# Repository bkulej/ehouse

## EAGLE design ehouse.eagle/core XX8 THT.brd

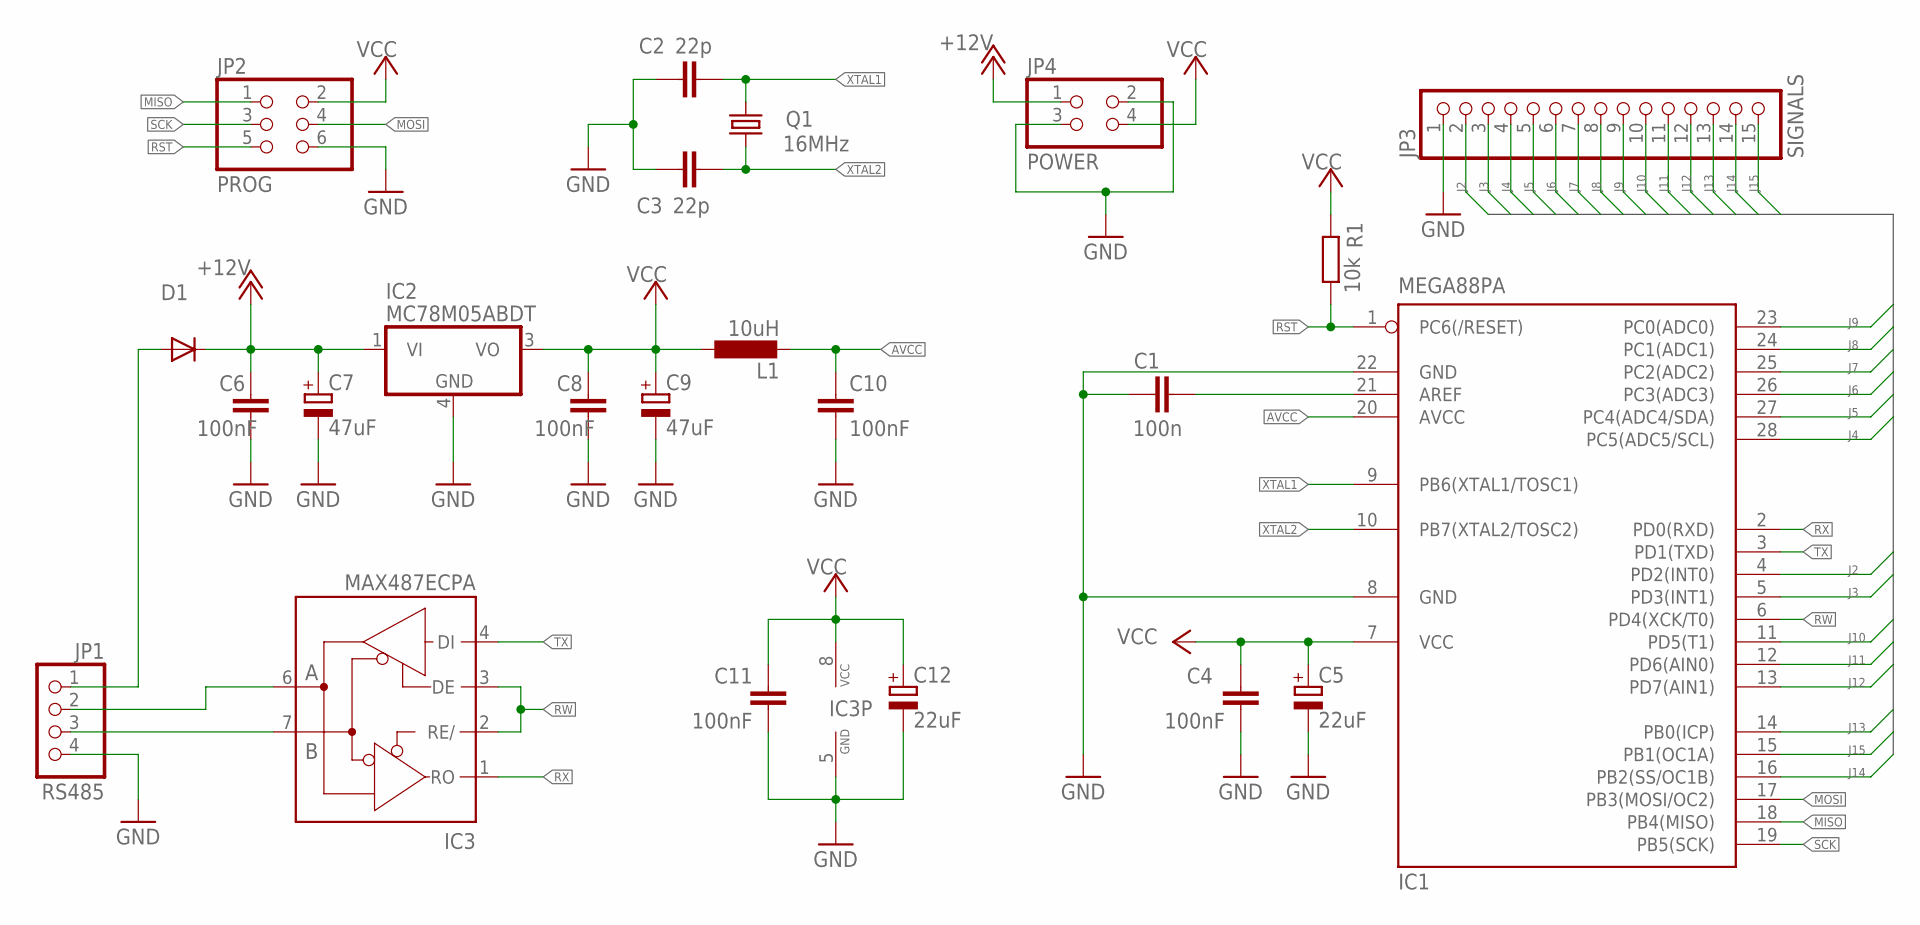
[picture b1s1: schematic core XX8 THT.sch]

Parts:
C1: 100n; C025-024X044
C2, C3: 22p; C025-024X044
C4, C6, C8, C10, C11: 100nF; C025-025X050
C5, C12: 22uF; E2-5
C7, C9: 47uF; E2,5-6
D1: 1N4002; DO34-7
IC1: MEGA88PA; DIL28-3
IC2: MC78M05ABDT; DPACK_3
IC3: MAX487ECPA; DIL08
JP1: RS485; 1X04
JP2: PROG; 2X03
JP3: SIGNALS; 1X15
JP4: POWER; 2X02
L1: 10uH; 0207/12
Q1: 16MHz; HC49/S
R1: 10k; 0204V

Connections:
+12V: C6.1, C7.+, D1.C, IC2.1 (VI), JP4.1
AVCC: C10.1, IC1.20 (AVCC), L1.2
GND: C1.1, C2.1, C3.1, C4.2, C5.-, C6.2, C7.-, C8.2, C9.-, C10.2, C11.2, C12.-, IC1.8 (GND), IC1.22 (GND), IC2.4 (GND), IC3.5 (GND), JP1.4, JP2.6, JP3.1, JP4.2, JP4.3
J2: IC1.4 (PD2(INT0)), JP3.2
J3: IC1.5 (PD3(INT1)), JP3.3
J4: IC1.28 (PC5(ADC5/SCL)), JP3.4
J5: IC1.27 (PC4(ADC4/SDA)), JP3.5
J6: IC1.26 (PC3(ADC3)), JP3.6
J7: IC1.25 (PC2(ADC2)), JP3.7
J8: IC1.24 (PC1(ADC1)), JP3.8
J9: IC1.23 (PC0(ADC0)), JP3.9
J10: IC1.11 (PD5(T1)), JP3.10
J11: IC1.12 (PD6(AIN0)), JP3.11
J12: IC1.13 (PD7(AIN1)), JP3.12
J13: IC1.14 (PB0(ICP)), JP3.13
J14: IC1.16 (PB2(SS/OC1B)), JP3.14
J15: IC1.15 (PB1(OC1A)), JP3.15
MISO: IC1.18 (PB4(MISO)), JP2.1
MOSI: IC1.17 (PB3(MOSI/OC2)), JP2.4
unnamed: C1.2, IC1.21 (AREF)
unnamed: D1.A, JP1.1
unnamed: IC3.7 (B), JP1.3
unnamed: IC3.6 (A), JP1.2
RST: IC1.1 (PC6(/RESET)), JP2.5, R1.1
RW: IC1.6 (PD4(XCK/T0)), IC3.2 (RE/), IC3.3 (DE)
RX: IC1.2 (PD0(RXD)), IC3.1 (RO)
SCK: IC1.19 (PB5(SCK)), JP2.3
TX: IC1.3 (PD1(TXD)), IC3.4 (DI)
VCC: C4.1, C5.+, C8.1, C9.+, C11.1, C12.+, IC1.7 (VCC), IC2.3 (VO), IC3.8 (VCC), JP2.2, JP4.4, L1.1, R1.2
XTAL1: C2.2, IC1.9 (PB6(XTAL1/TOSC1)), Q1.2
XTAL2: C3.2, IC1.10 (PB7(XTAL2/TOSC2)), Q1.1

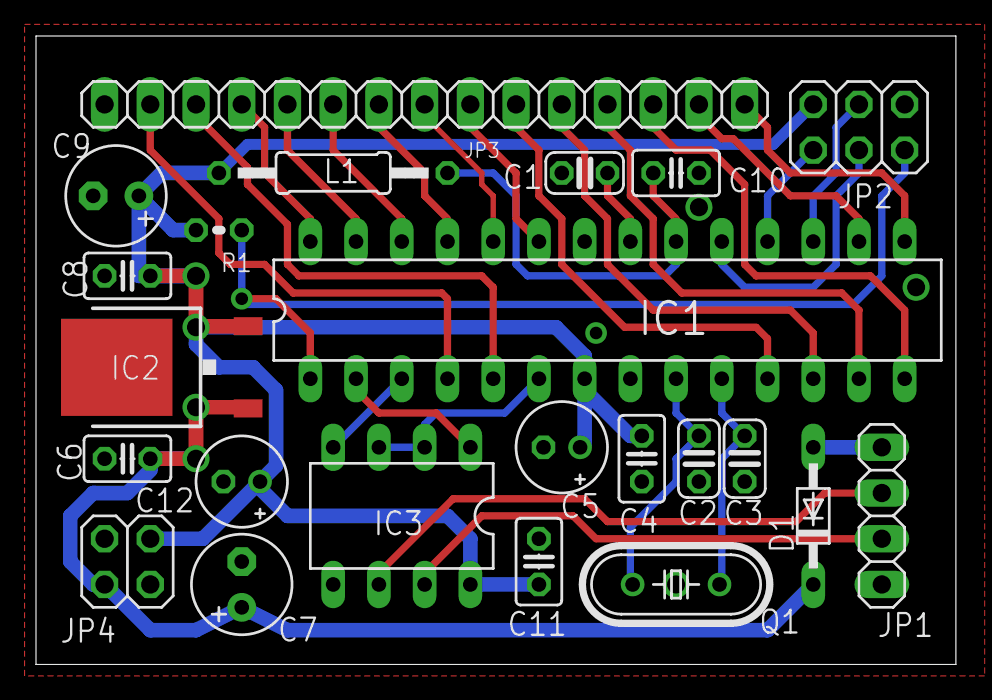
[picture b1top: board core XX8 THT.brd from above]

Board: 2 copper layers, 51.1 x 34.9 mm, 23 parts (0 on the bottom side), 31 nets.

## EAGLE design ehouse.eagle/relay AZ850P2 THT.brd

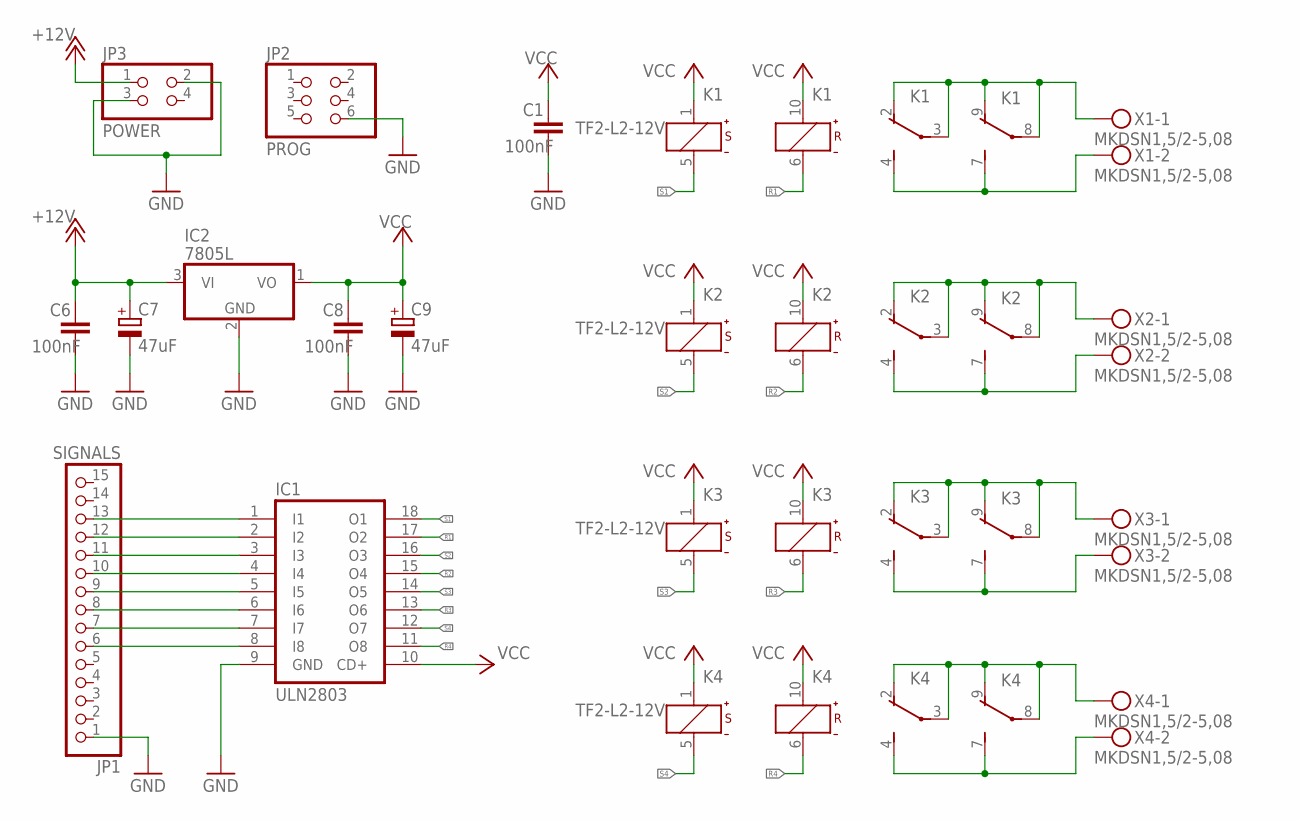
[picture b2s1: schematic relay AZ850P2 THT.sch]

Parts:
C1, C6, C8: 100nF; C025-025X050
C7, C9: 47uF; E2,5-6
IC1: ULN2803; DIL18
IC2: 7805L; TO92
JP1: SIGNALS; 1X15
JP2: PROG; 2X03
JP3: POWER; 2X02
K1, K2, K3, K4: TF2-L2-12V; TF2
X1, X2, X3, X4: MKDSN1,5/2-5,08

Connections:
+12V: C6.1, C7.+, IC2.3 (VI), JP3.1
GND: C1.2, C6.2, C7.-, C8.2, C9.-, IC1.9 (GND), IC2.2 (GND), JP1.1, JP2.6, JP3.2, JP3.3
unnamed: IC1.1 (I1), JP1.13
unnamed: IC1.2 (I2), JP1.12
unnamed: IC1.3 (I3), JP1.11
unnamed: IC1.4 (I4), JP1.10
unnamed: IC1.5 (I5), JP1.9
unnamed: IC1.6 (I6), JP1.8
unnamed: IC1.7 (I7), JP1.7
unnamed: IC1.8 (I8), JP1.6
unnamed: K1.2 (O), K1.3, K1.8, K1.9 (O), X1.1
unnamed: K1.4 (S), K1.7 (S), X1.2
unnamed: K2.2 (O), K2.3, K2.8, K2.9 (O), X2.1
unnamed: K2.4 (S), K2.7 (S), X2.2
unnamed: K3.2 (O), K3.3, K3.8, K3.9 (O), X3.1
unnamed: K3.4 (S), K3.7 (S), X3.2
unnamed: K4.4 (S), K4.7 (S), X4.2
unnamed: K4.2 (O), K4.3, K4.8, K4.9 (O), X4.1
R1: IC1.17 (O2), K1.6 (-)
R2: IC1.15 (O4), K2.6 (-)
R3: IC1.13 (O6), K3.6 (-)
R4: IC1.11 (O8), K4.6 (-)
S1: IC1.18 (O1), K1.5 (-)
S2: IC1.16 (O3), K2.5 (-)
S3: IC1.14 (O5), K3.5 (-)
S4: IC1.12 (O7), K4.5 (-)
VCC: C1.1, C8.1, C9.+, IC1.10 (CD+), IC2.1 (VO), K1.1 (+), K1.10 (+), K2.1 (+), K2.10 (+), K3.1 (+), K3.10 (+), K4.1 (+), K4.10 (+)

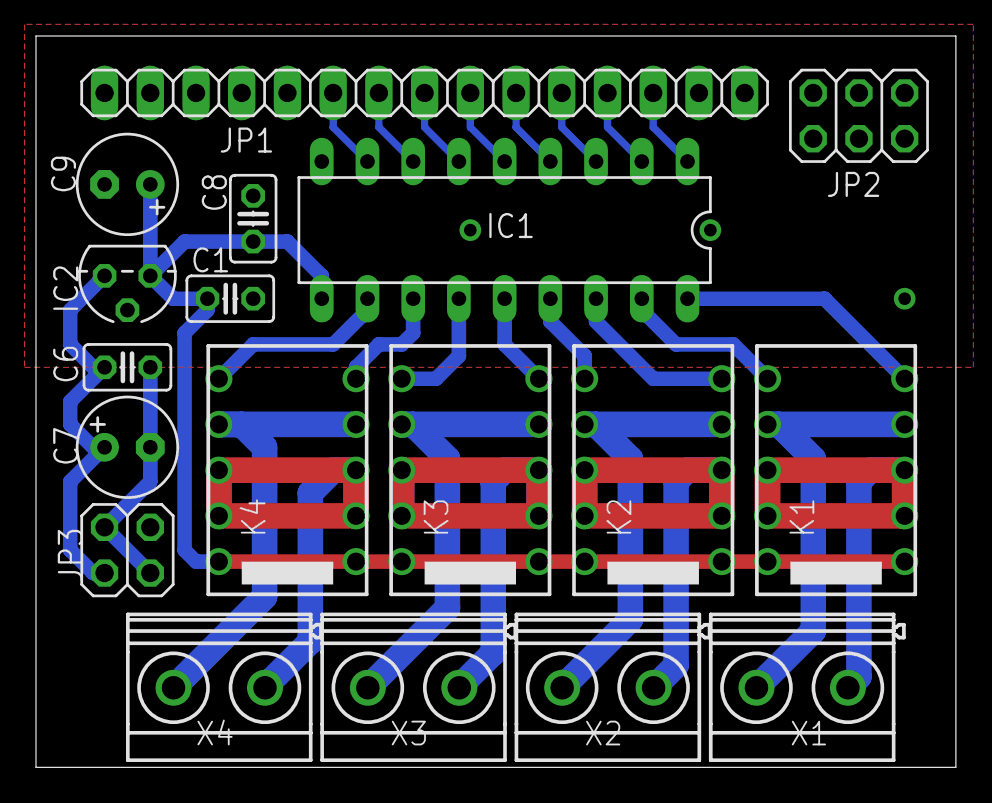
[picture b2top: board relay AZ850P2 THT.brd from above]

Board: 2 copper layers, 51.1 x 40.6 mm, 18 parts (0 on the bottom side), 27 nets.

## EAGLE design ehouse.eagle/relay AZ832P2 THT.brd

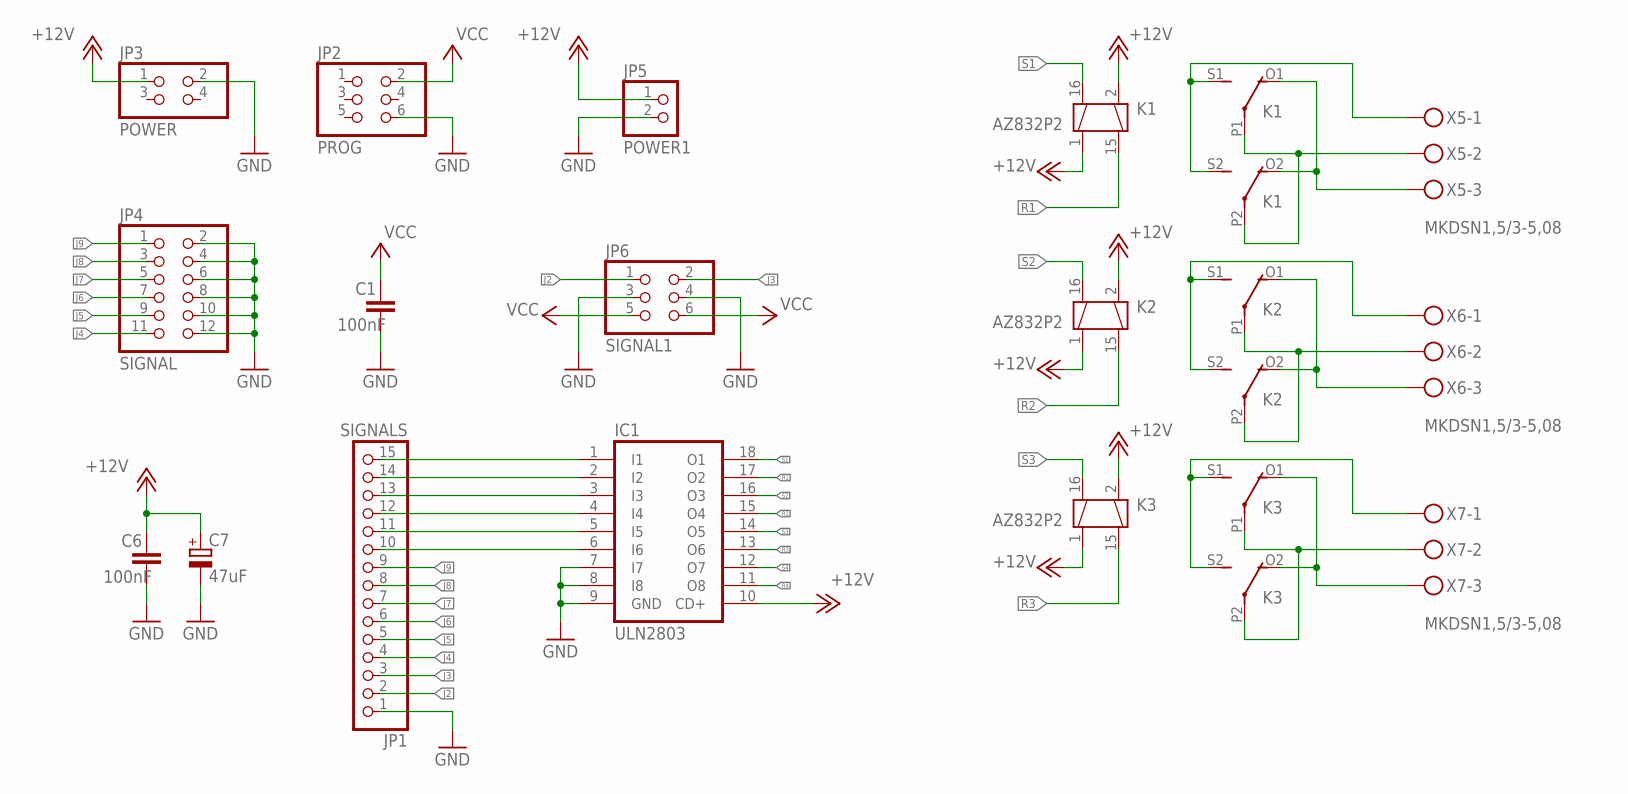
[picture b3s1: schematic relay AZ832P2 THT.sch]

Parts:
C1, C6: 100nF; C025-025X050
C7: 47uF; E2,5-6
IC1: ULN2803; DIL18
JP1: SIGNALS; 1X15
JP2: PROG; 2X03
JP3: POWER; 2X02
JP4: SIGNAL; 2X06
JP5: POWER1; 1X02
JP6: SIGNAL1; 2X03
K1, K2, K3: AZ832P2; DS2E-L2
X5, X6, X7: MKDSN1,5/3-5,08

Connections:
+12V: C6.1, C7.+, IC1.10 (CD+), JP3.1, JP5.1, K1.1 (2), K1.2 (3), K2.1 (2), K2.2 (3), K3.1 (2), K3.2 (3)
GND: C1.2, C6.2, C7.-, IC1.7 (I7), IC1.8 (I8), IC1.9 (GND), JP1.1, JP2.6, JP3.2, JP4.2, JP4.4, JP4.6, JP4.8, JP4.10, JP4.12, JP5.2, JP6.3, JP6.4
J2: JP1.2, JP6.1
J3: JP1.3, JP6.2
J4: JP1.4, JP4.11
J5: JP1.5, JP4.9
J6: JP1.6, JP4.7
J7: JP1.7, JP4.5
J8: JP1.8, JP4.3
J9: JP1.9, JP4.1
unnamed: IC1.1 (I1), JP1.15
unnamed: IC1.2 (I2), JP1.14
unnamed: IC1.3 (I3), JP1.13
unnamed: IC1.4 (I4), JP1.12
unnamed: IC1.5 (I5), JP1.11
unnamed: IC1.6 (I6), JP1.10
unnamed: K1.S1 (S), K1.S2 (S), X5.1
unnamed: K2.S1 (S), K2.S2 (S), X6.1
unnamed: K3.S1 (S), K3.S2 (S), X7.1
unnamed: K3.P1, K3.P2, X7.2
unnamed: K2.P1, K2.P2, X6.2
unnamed: K1.O1 (O), K1.O2 (O), X5.3
unnamed: K2.O1 (O), K2.O2 (O), X6.3
unnamed: K1.P1, K1.P2, X5.2
unnamed: K3.O1 (O), K3.O2 (O), X7.3
R1: IC1.17 (O2), K1.15 (4)
R2: IC1.15 (O4), K2.15 (4)
R3: IC1.13 (O6), K3.15 (4)
R4: IC1.11 (O8)
S1: IC1.18 (O1), K1.16 (1)
S2: IC1.16 (O3), K2.16 (1)
S3: IC1.14 (O5), K3.16 (1)
S4: IC1.12 (O7)
VCC: C1.1, JP2.2, JP6.5, JP6.6

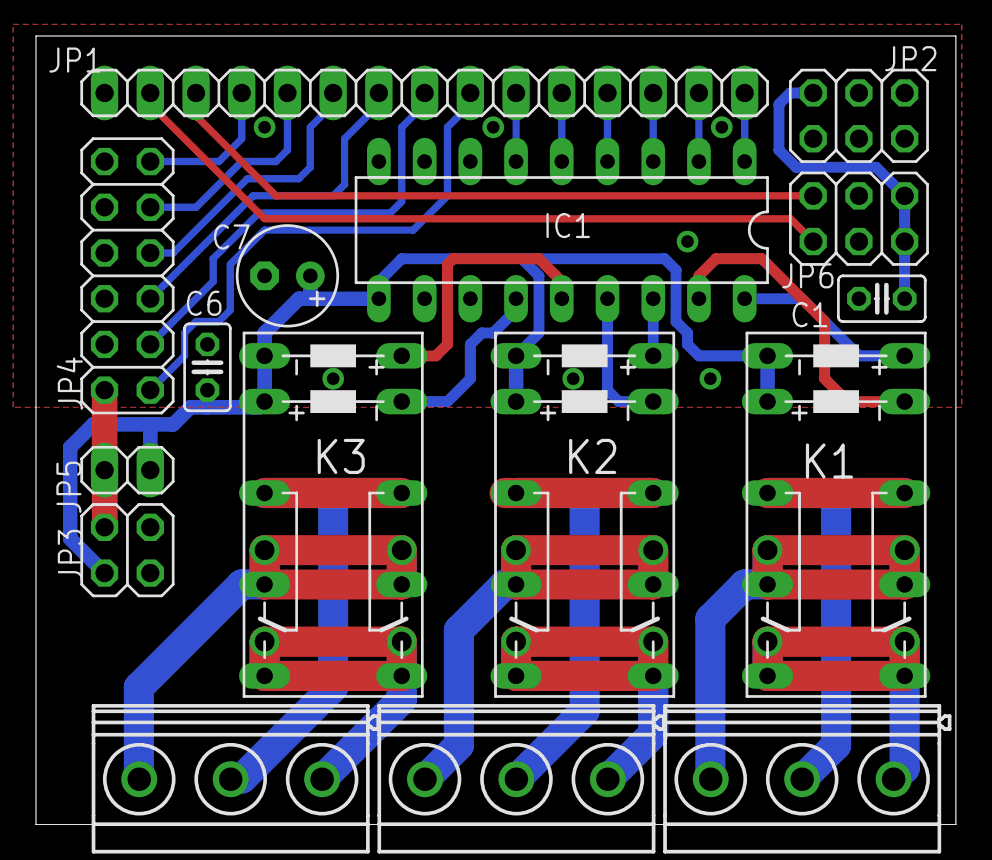
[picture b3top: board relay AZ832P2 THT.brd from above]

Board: 2 copper layers, 51.1 x 43.8 mm, 16 parts (0 on the bottom side), 32 nets.

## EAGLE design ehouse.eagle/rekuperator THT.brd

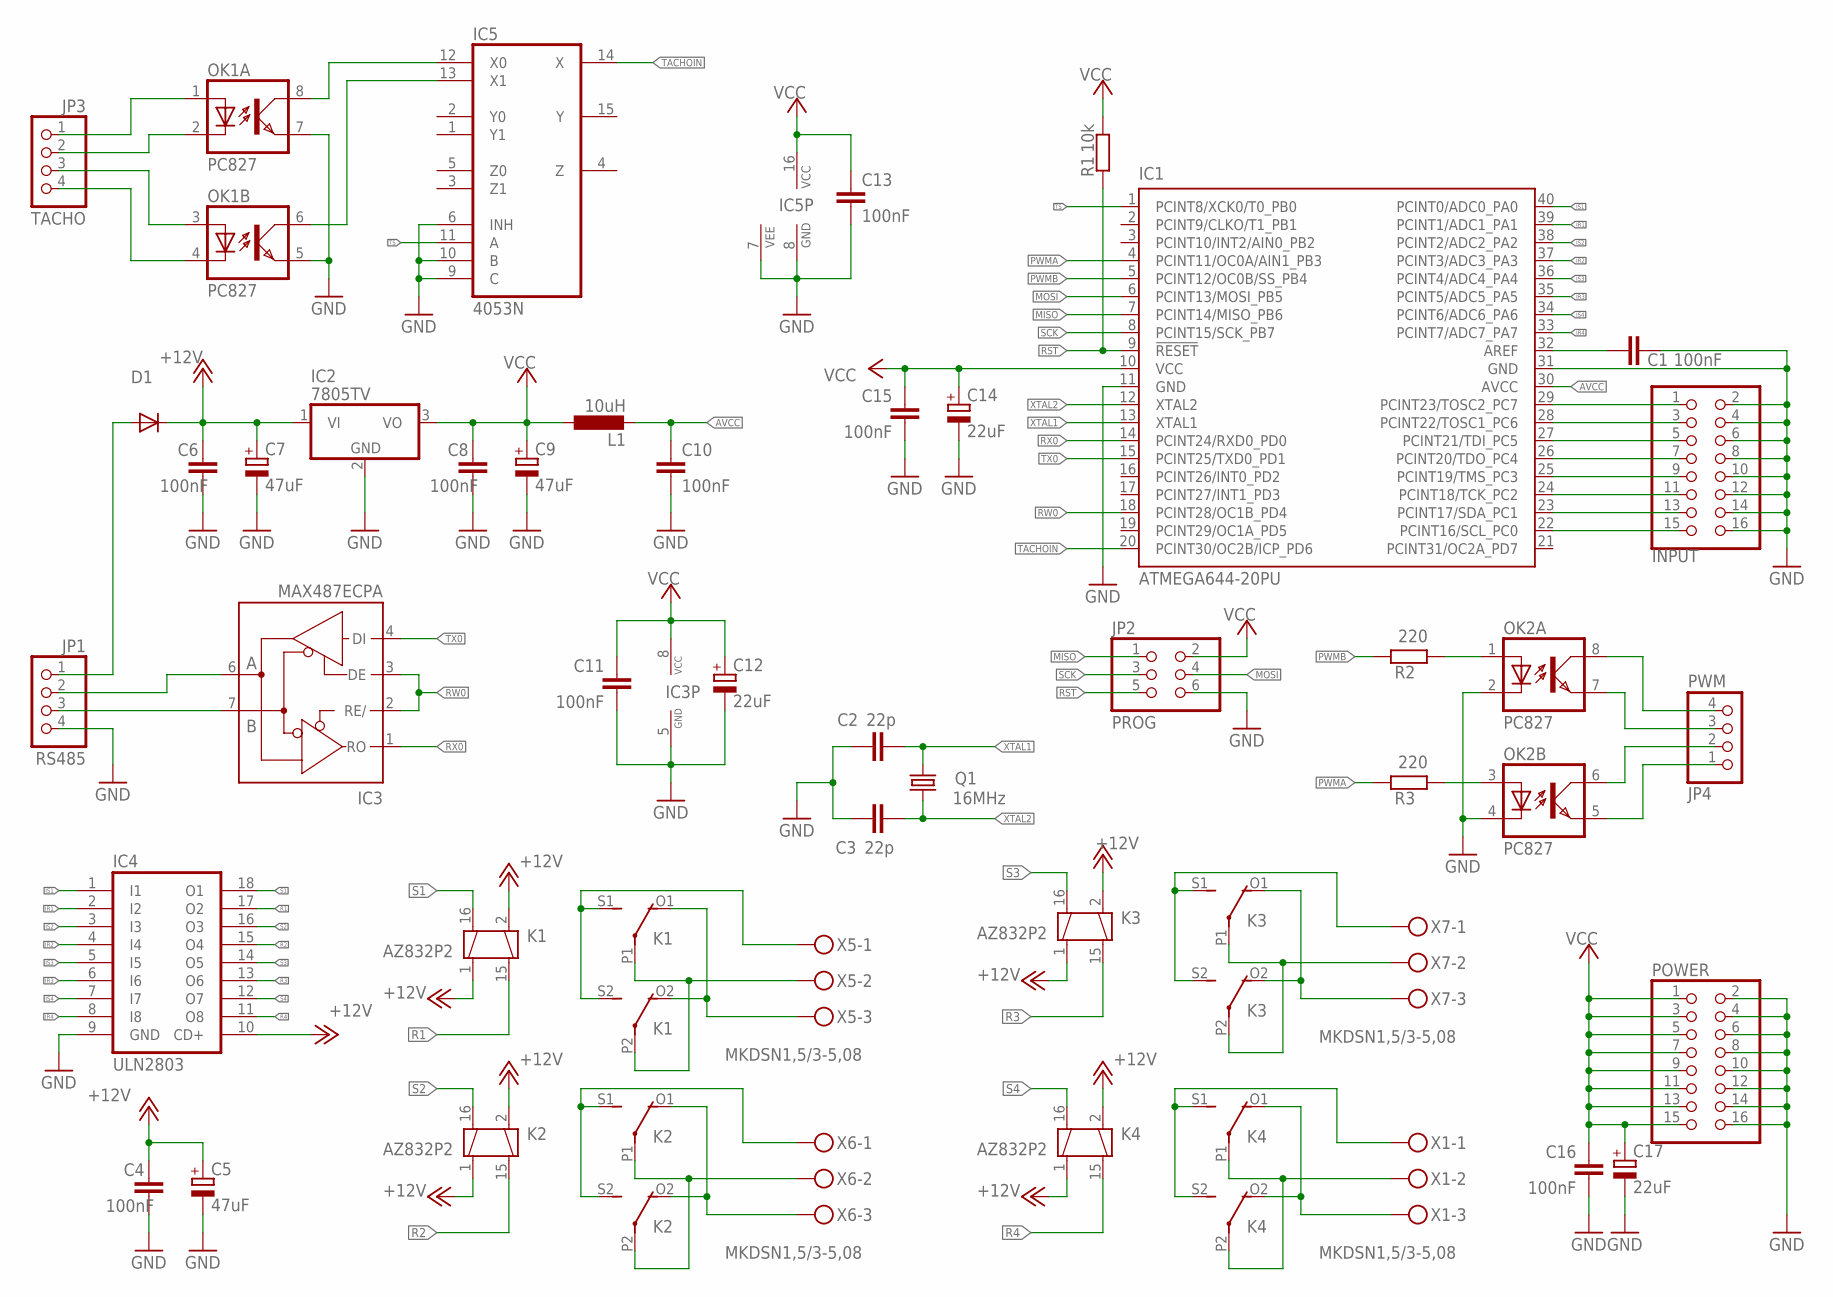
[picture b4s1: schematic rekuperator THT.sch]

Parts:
C1, C4, C6, C8, C10, C11, C13, C15, C16: 100nF; C025-025X050
C2, C3: 22p; C025-024X044
C5, C7, C9: 47uF; E2,5-6
C12, C14, C17: 22uF; E2-5
D1: 1N4002; DO34-7
IC1: ATMEGA644-20PU; DIL40
IC2: 7805TV; TO220V
IC3: MAX487ECPA; DIL08
IC4: ULN2803; DIL18
IC5: 4053N; DIL16
INPUT: PINHD-2X8; 2X08
JP1: RS485; 1X04
JP2: PROG; 2X03
JP3: TACHO; 1X04
JP4: PWM; 1X04
K1, K2, K3, K4: AZ832P2; DS2E-L2
L1: 10uH; 0207/12
OK1, OK2: PC827; DIL08
POWER: PINHD-2X8; 2X08
Q1: 16MHz; HC49/S
R1: 10k; 0204V
R2, R3: 220; 0207/12
X1, X5, X6, X7: MKDSN1,5/3-5,08

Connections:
+12V: C4.1, C5.+, C6.1, C7.+, D1.C, IC2.1 (VI), IC4.10 (CD+), K1.1 (2), K1.2 (3), K2.1 (2), K2.2 (3), K3.1 (2), K3.2 (3), K4.1 (2), K4.2 (3)
AVCC: C10.1, IC1.30 (AVCC), L1.2
GND: C1.2, C2.1, C3.1, C4.2, C5.-, C6.2, C7.-, C8.2, C9.-, C10.2, C11.2, C12.-, C13.2, C14.-, C15.2, C16.2, C17.-, IC1.11 (GND), IC1.31 (GND), IC2.2 (GND), IC3.5 (GND), IC4.9 (GND), IC5.6 (INH), IC5.7 (VEE), IC5.8 (GND), IC5.9 (C), IC5.10 (B), INPUT.2, INPUT.4, INPUT.6, INPUT.8, INPUT.10, INPUT.12, INPUT.14, INPUT.16, JP1.4, JP2.6, OK1.5 (EMIT), OK1.7 (EMIT), OK2.2 (C), OK2.4 (C), POWER.2, POWER.4, POWER.6, POWER.8, POWER.10, POWER.12, POWER.14, POWER.16
IR1: IC1.39 (PCINT1/ADC1_PA1), IC4.2 (I2)
IR2: IC1.37 (PCINT3/ADC3_PA3), IC4.4 (I4)
IR3: IC1.35 (PCINT5/ADC5_PA5), IC4.6 (I6)
IR4: IC1.33 (PCINT7/ADC7_PA7), IC4.8 (I8)
IS1: IC1.40 (PCINT0/ADC0_PA0), IC4.1 (I1)
IS2: IC1.38 (PCINT2/ADC2_PA2), IC4.3 (I3)
IS3: IC1.36 (PCINT4/ADC4_PA4), IC4.5 (I5)
IS4: IC1.34 (PCINT6/ADC6_PA6), IC4.7 (I7)
MISO: IC1.7 (PCINT14/MISO_PB6), JP2.1
MOSI: IC1.6 (PCINT13/MOSI_PB5), JP2.4
unnamed: K4.S1 (S), K4.S2 (S), X1.1
unnamed: K4.P1, K4.P2, X1.2
unnamed: D1.A, JP1.1
unnamed: IC3.7 (B), JP1.3
unnamed: IC3.6 (A), JP1.2
unnamed: K4.O1 (O), K4.O2 (O), X1.3
unnamed: C1.1, IC1.32 (AREF)
unnamed: IC5.12 (X0), OK1.8 (COL)
unnamed: K1.S1 (S), K1.S2 (S), X5.1
unnamed: K2.S1 (S), K2.S2 (S), X6.1
unnamed: K3.S1 (S), K3.S2 (S), X7.1
unnamed: IC5.13 (X1), OK1.6 (COL)
unnamed: K3.P1, K3.P2, X7.2
unnamed: K2.P1, K2.P2, X6.2
unnamed: K1.O1 (O), K1.O2 (O), X5.3
unnamed: K2.O1 (O), K2.O2 (O), X6.3
unnamed: JP3.2, OK1.2 (C)
unnamed: K1.P1, K1.P2, X5.2
unnamed: K3.O1 (O), K3.O2 (O), X7.3
unnamed: JP3.1, OK1.1 (A)
unnamed: JP3.3, OK1.3 (A)
unnamed: JP3.4, OK1.4 (C)
unnamed: JP4.3, OK2.7 (EMIT)
unnamed: JP4.2, OK2.6 (COL)
unnamed: OK2.1 (A), R2.2
unnamed: OK2.3 (A), R3.2
unnamed: JP4.4, OK2.8 (COL)
unnamed: JP4.1, OK2.5 (EMIT)
unnamed: IC1.29 (PCINT23/TOSC2_PC7), INPUT.1
unnamed: IC1.28 (PCINT22/TOSC1_PC6), INPUT.3
unnamed: IC1.27 (PCINT21/TDI_PC5), INPUT.5
unnamed: IC1.26 (PCINT20/TDO_PC4), INPUT.7
unnamed: IC1.25 (PCINT19/TMS_PC3), INPUT.9
unnamed: IC1.24 (PCINT18/TCK_PC2), INPUT.11
unnamed: IC1.23 (PCINT17/SDA_PC1), INPUT.13
unnamed: IC1.22 (PCINT16/SCL_PC0), INPUT.15
PWMA: IC1.4 (PCINT11/OC0A/AIN1_PB3), R3.1
PWMB: IC1.5 (PCINT12/OC0B/SS_PB4), R2.1
R1: IC4.17 (O2), K1.15 (4)
R2: IC4.15 (O4), K2.15 (4)
R3: IC4.13 (O6), K3.15 (4)
R4: IC4.11 (O8), K4.15 (4)
RST: IC1.9 (!RESET), JP2.5, R1.2
RW0: IC1.18 (PCINT28/OC1B_PD4), IC3.2 (RE/), IC3.3 (DE)
RX0: IC1.14 (PCINT24/RXD0_PD0), IC3.1 (RO)
S1: IC4.18 (O1), K1.16 (1)
S2: IC4.16 (O3), K2.16 (1)
S3: IC4.14 (O5), K3.16 (1)
S4: IC4.12 (O7), K4.16 (1)
SCK: IC1.8 (PCINT15/SCK_PB7), JP2.3
TACHOIN: IC1.20 (PCINT30/OC2B/ICP_PD6), IC5.14 (X)
TS: IC1.1 (PCINT8/XCK0/T0_PB0), IC5.11 (A)
TX0: IC1.15 (PCINT25/TXD0_PD1), IC3.4 (DI)
VCC: C8.1, C9.+, C11.1, C12.+, C13.1, C14.+, C15.1, C16.1, C17.+, IC1.10 (VCC), IC2.3 (VO), IC3.8 (VCC), IC5.16 (VCC), JP2.2, L1.1, POWER.1, POWER.3, POWER.5, POWER.7, POWER.9, POWER.11, POWER.13, POWER.15, R1.1
XTAL1: C2.2, IC1.13 (XTAL1), Q1.2
XTAL2: C3.2, IC1.12 (XTAL2), Q1.1

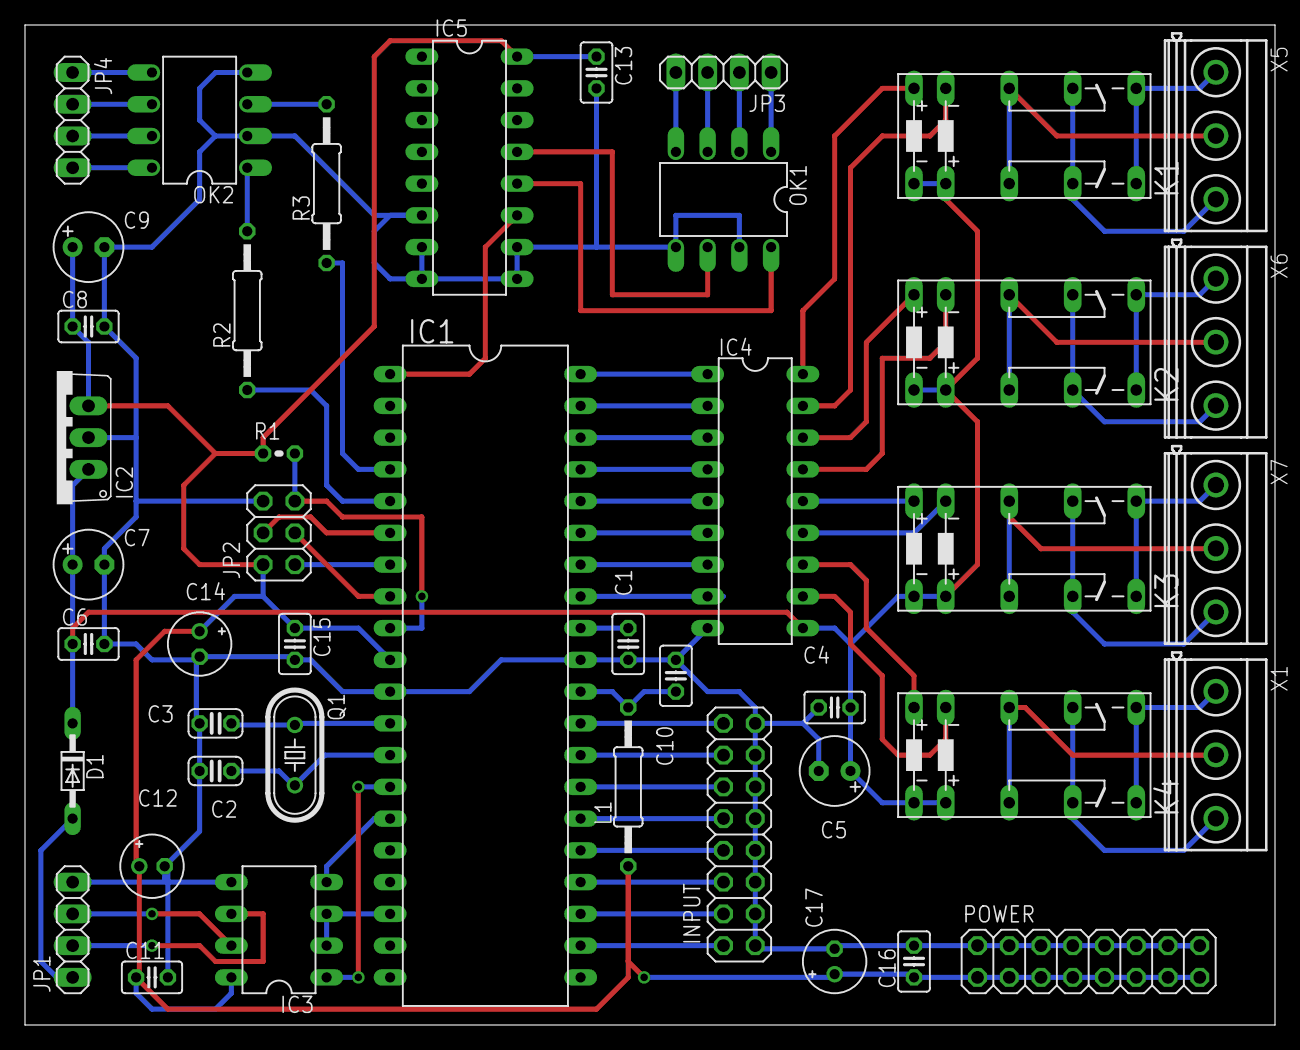
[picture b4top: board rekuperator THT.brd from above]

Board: 2 copper layers, 100.0 x 80.0 mm, 44 parts (0 on the bottom side), 69 nets.

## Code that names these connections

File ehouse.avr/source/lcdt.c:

#define LCDT_BODY

#include "devices.h"
#include "debug.h"
#include "lcdt.h"
#include "utils.h"
#include <inttypes.h>
#include <avr/io.h>
   
#ifdef LCDT_MODULE

#if MCU_XXX8	
	#define LCD_DDR			DDRC
	#define LCD_PORT 		PORTC
	#define LCD_PIN_EN 		PC4                   
	#define LCD_PIN_RS 		PC5	
#endif

#if MCU_XXX4
	#define LCD_DDR			DDRC
	#define LCD_PORT 		PORTC
	#define LCD_PIN_EN 		PC3                   
	#define LCD_PIN_RS 		PC2
#endif

void lcdtWrite(uint8_t data) { 		
	LCD_PORT |= _BV(LCD_PIN_EN);	
#if MCU_XXX8
	LCD_PORT = ((LCD_PORT & 0xF0) | (data & 0xF0) >> 4);	
#endif
#if MCU_XXX4
	LCD_PORT = ((LCD_PORT & 0x0F) | (data & 0xF0));	
#endif
	LCD_PORT &= ~_BV(LCD_PIN_EN);
	asm("nop");	
	LCD_PORT |= _BV(LCD_PIN_EN);	
#if MCU_XXX8		
	LCD_PORT = ((LCD_PORT & 0xF0) | (data & 0x0F));	
#endif
#if MCU_XXX4	
	LCD_PORT = ((LCD_PORT & 0x0F) | ((data & 0x0F) << 4));		
#endif
	LCD_PORT &= ~_BV(LCD_PIN_EN);
	asm("nop");	
	LCD_PORT |= _BV(LCD_PIN_EN);	
	utilsDelayMs(1);
}


void lcdtCommand(uint8_t data) { 
	LCD_PORT &= ~_BV(LCD_PIN_RS);
	lcdtWrite(data);	
	utilsDelayMs(10);
} 


void lcdtInit() { 	
	utilsDelayMs(200);
	// Ustawienie wyjsc
#if MCU_XXX8
	LCD_DDR |= 0x0F;
#endif
#if MCU_XXX4
	LCD_DDR |= 0xF0;	
#endif	
	LCD_DDR |= _BV(LCD_PIN_EN);
	LCD_DDR |= _BV(LCD_PIN_RS);		
	// Wyzerowanie sterowania
	LCD_PORT &= ~_BV(LCD_PIN_EN);
	LCD_PORT &= ~_BV(LCD_PIN_RS);
	utilsDelayMs(10);
	LCD_PORT |= _BV(LCD_PIN_EN);
	LCD_PORT |= _BV(LCD_PIN_RS);
	// Ustawienie wyswietlacza	
	lcdtCommand(0x30); // interfejs 4-bity, 2-linie, znak 5x7 
	lcdtCommand(0x28); // interfejs 4-bity, 2-linie, znak 5x7 
	lcdtCommand(0x28); // interfejs 4-bity, 2-linie, znak 5x7 
	lcdtCommand(0x08); // wy³¹cz LCD, kursor i miganie 
	lcdtCommand(0x01); // czyæ LCD 
	lcdtCommand(0x06); // bez przesuwania w prawo 
	lcdtCommand(0x0C); // w³¹cz LCD, bez kursora i mrugania 
	utilsDelayMs(10);	
}
 

void lcdtText(char* text) { 	
	LCD_PORT |= _BV(LCD_PIN_RS);
	while(*text) { 
  		lcdtWrite(*text);
  		text++;
  	} 
} 

/* Konwertuje liczbe ca³kowit¹ na string. Mozna przekonwertowac float mno¿¹c
   liczbê przez 10,100,1000, .. i wstawiajac na odpowiednim miejscu przecinek
	param:
		in 		- liczba do konwersji
		out		- przekonwerotwany string
		length  - dlugoæ ci¹gu znaków
		comma	- na którym miejscu przecinek
*/
void lcdIntToString(int32_t in, char * out, uint8_t length, uint8_t comma ) {	
	char tmpout[10];
	// Ustalenie dlugosci
	int8_t len = length;
	if(comma){
		--len;
	}
	// Obliczenie wartosci bezwzglednej
	uint8_t negative;
	int32_t tmpin;	
	if(in < 0) {
		tmpin = in * -1;
		negative = 1;
		--len;
	} else {
		tmpin = in;
		negative = 0;
	}
	// Konwersja na liczbe
	for(int8_t i = 9; i >= 0; i--) {
		tmpout[i] = (tmpin % 10) + '0';
		tmpin /= 10;
	}	
	// Przepisanie wyniku
	uint8_t pos = 0;
	uint8_t nozero = 0;
	for(uint8_t i = 0; i<=9; i++) {		
		// pominiecie przednich zer
		if((tmpout[i] != '0') || (9-i == comma)) {
			nozero = 1;
		}
		// wstawienie minusa
		if(nozero && negative) {
			out[pos++] = '-';			
			negative = 0;
		}
		// wstawienie spacji wymuszonej d³ugoci
		if(!nozero && (len > 0) && (9-i < len)) {
			out[pos++]=' ';			
		}
		// wstawienie przecinka
		if((comma > 0) && (9-i == comma-1)) {
			out[pos++]=',';			
		}
		// przepisanie znaku
		if(nozero) {
			out[pos++] = tmpout[i];			
		}
	}
	out[pos]= 0;
}


void lcdtInt(int32_t in, uint8_t length, uint8_t comma) {
	char tmp[12];
	lcdIntToString(in,tmp, length, comma);		
	lcdtText(tmp);
}


void lcdtXY(uint8_t x, uint8_t y) { 
   lcdtCommand((x*0x40+y) | 0x80); 
}           	


void lcdtClear() {
	lcdtCommand(0x01);
}

#endif

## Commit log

2018-11-19 Changing the atmosphere library
2018-11-19 Additional logging of messages
2018-11-19 Adding gwt.properties
2018-11-20 Format code
2018-11-20 Code refactoring
2018-11-20 Change of project names
2018-11-22 Change of message handling via socket
2018-11-22 Change in .gitignore
2018-11-25 Changing Spring Boot version
2018-12-16 the skeleton of the project
2018-12-23 Message conversion
2018-12-26 Messages converter
2018-12-26 Test refactoring
2019-05-19 change of java version to 11 and springboot to 2.1.5
2019-05-19 Add stoping to threads Additional spring configuration metadata Spring injection by constructor Remove many inspect code error and warnings
2019-05-20 Remove @SuppressWarnings("ALL") from IntelliJ
2019-05-20 Removing bug from eclipse
2019-05-20 Code refactoring for jdk 11
2019-05-21 Test repair
2019-05-21 Remove language attribute from htlm
2019-05-21 Start decoder developing
2019-05-21 Message decoder and message sender
2019-05-21 Intelj warnings
2019-05-22 Message decoder and sender
2019-05-24 Message reader
2019-06-20 Add AVR source
2019-06-20 Ehouse Eagle schema
2019-06-20 Boiler pump mode
2019-06-20 Ignore files i ehouse.avr
2019-06-20 Java 11
2019-06-20 Bug in closing socket
2019-09-22 Return to Java 8
2019-09-22 Upgrade Spring Boot
2019-09-29 Refactoring Receiving messages
2019-09-29 Message logger skeleton
2023-02-22 Bump commons-fileupload from 1.3.3 to 1.5 in /ehouse.gwt
    Bumps commons-fileupload from 1.3.3 to 1.5.
    ---
    updated-dependencies:
    - dependency-name: commons-fileupload:commons-fileupload
    dependency-type: direct:production
    ...
